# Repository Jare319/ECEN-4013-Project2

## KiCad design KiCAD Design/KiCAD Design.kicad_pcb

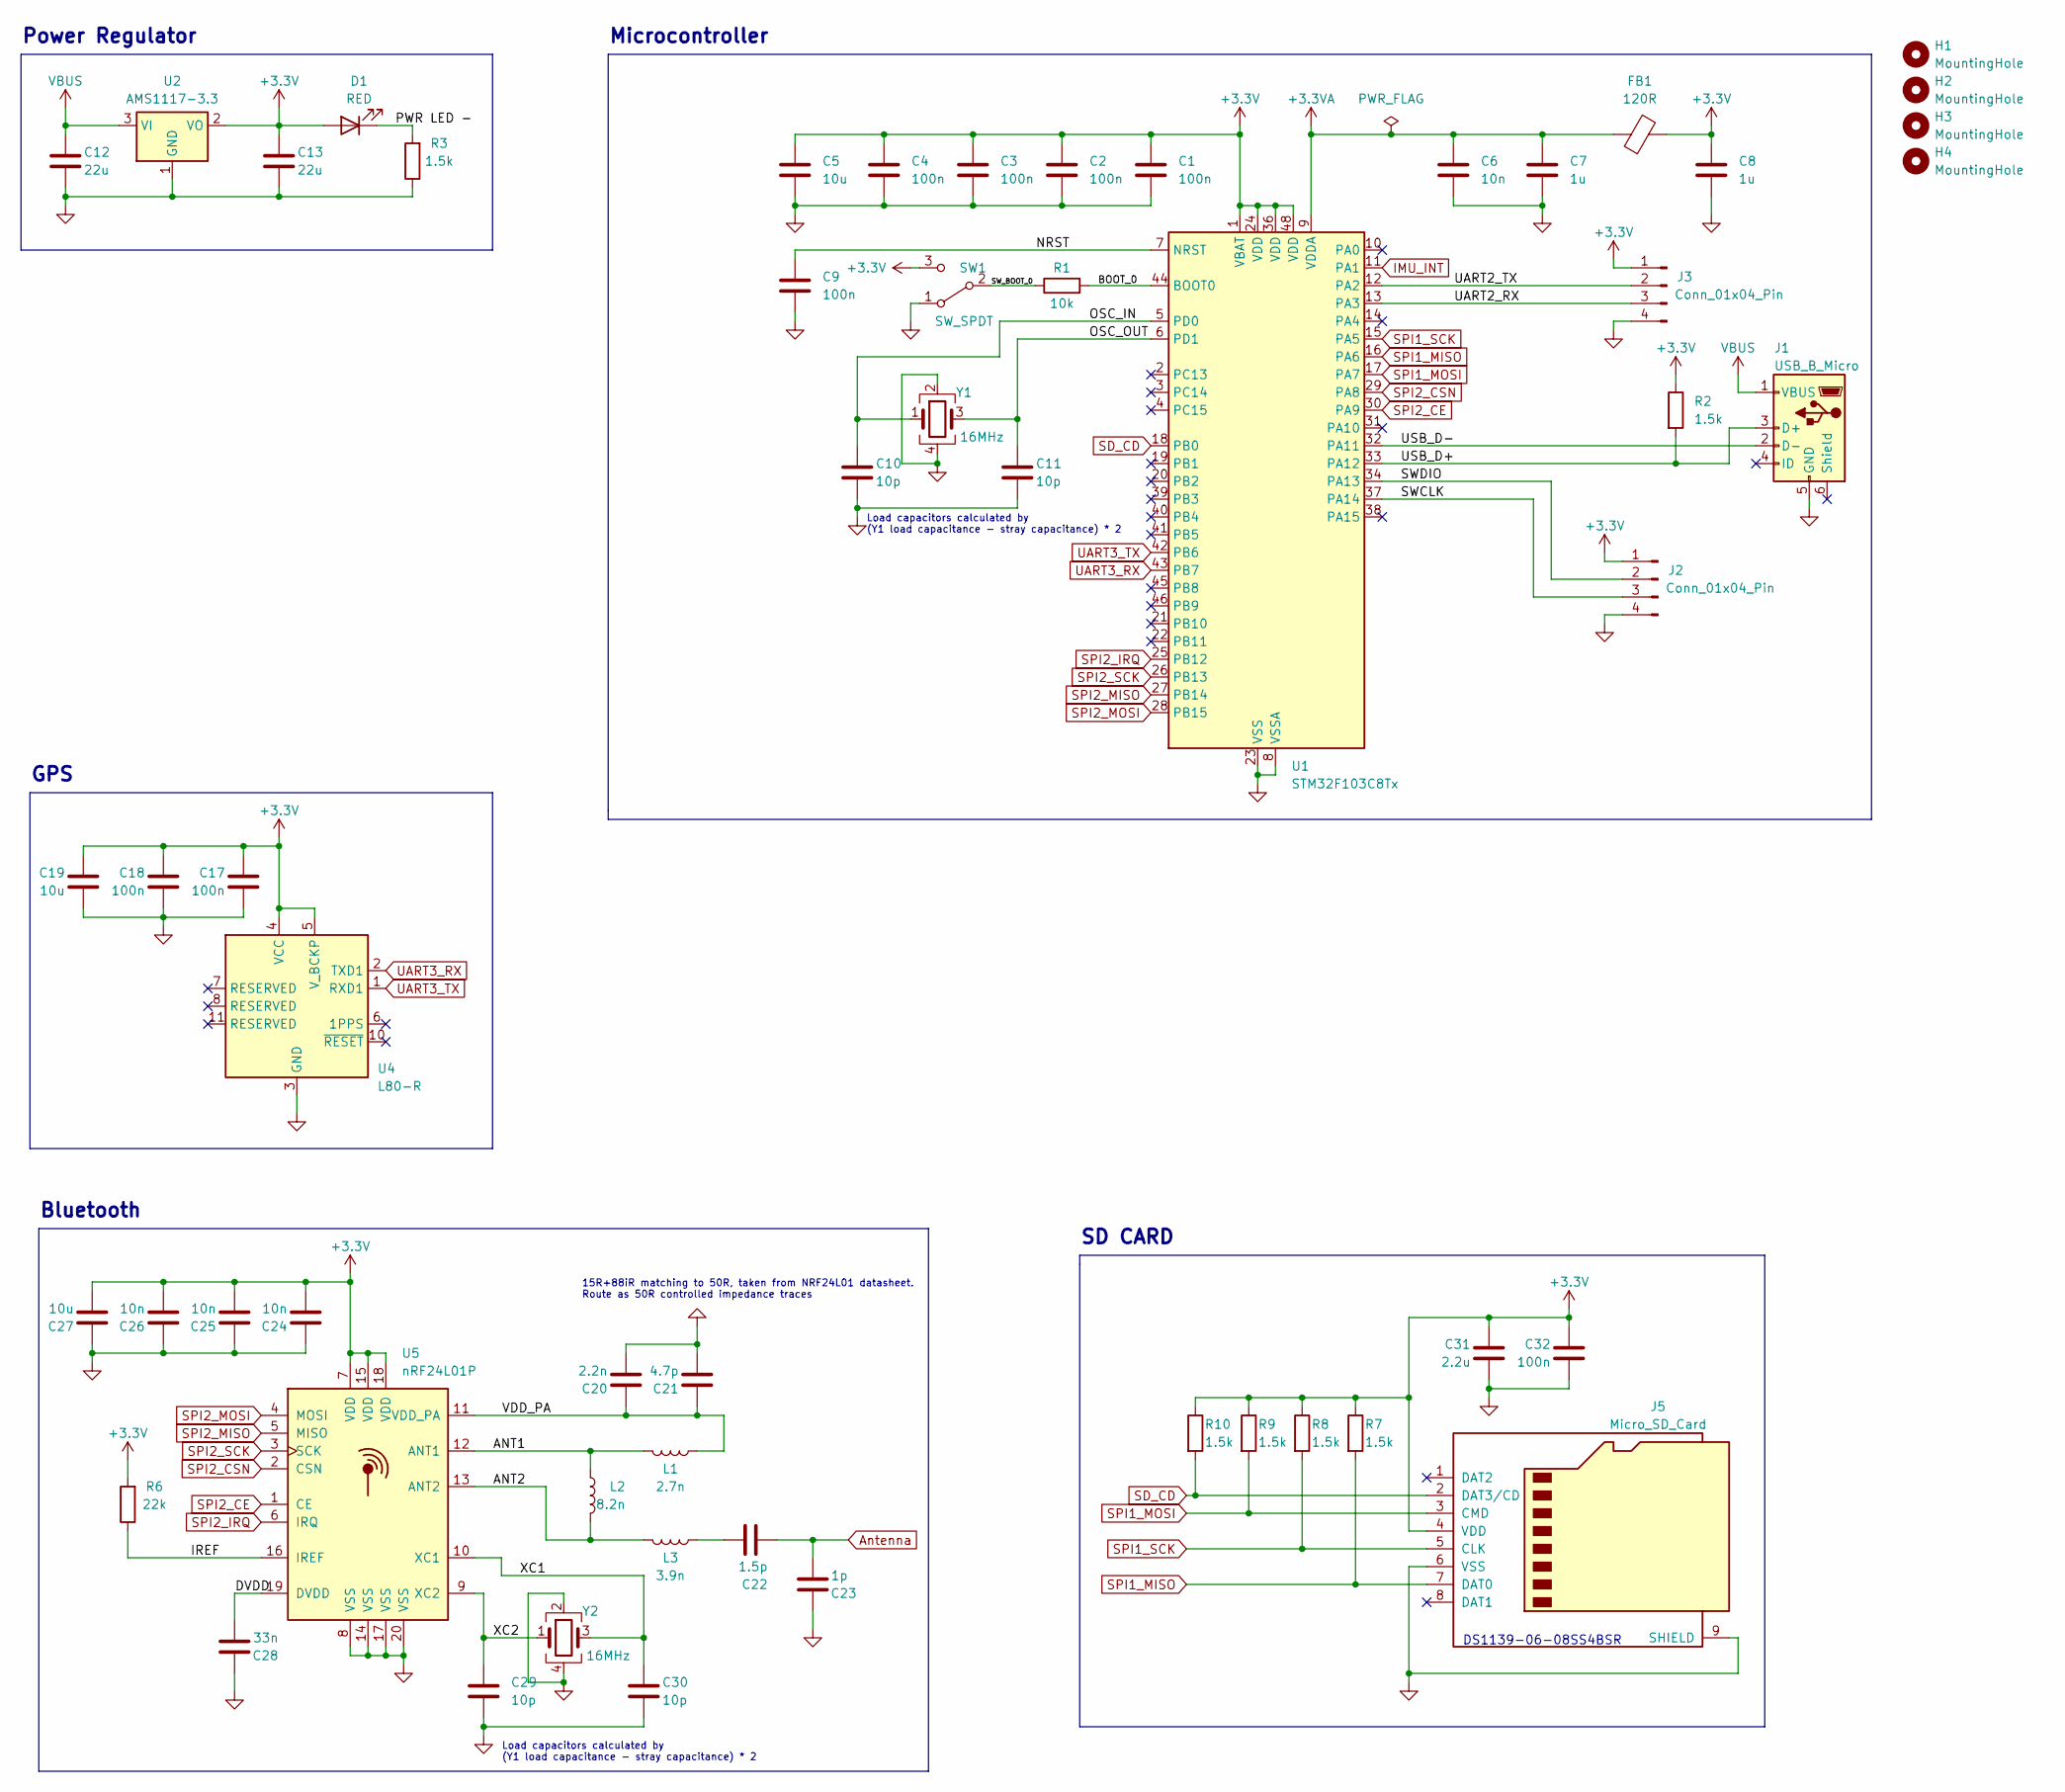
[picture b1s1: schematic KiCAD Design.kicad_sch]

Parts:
C1, C2, C3, C4, C9, C17, C18, C32: 100n; C_0402_1005Metric
C5, C19, C27: 10u; C_0603_1608Metric
C6, C24, C25, C26: 10n; C_0402_1005Metric
C7, C8: 1u; C_0402_1005Metric
C10, C11, C29, C30: 10p; C_0402_1005Metric
C12, C13: 22u; C_0805_2012Metric
C20: 2.2n; C_0402_1005Metric
C21: 4.7p; C_0402_1005Metric
C22: 1.5p; C_0402_1005Metric
C23: 1p; C_0402_1005Metric
C28: 33n; C_0402_1005Metric
C31: 2.2u; C_0402_1005Metric
D1: RED; LED_0603_1608Metric
FB1: 120R; L_0603_1608Metric
H1, H2, H3, H4: MountingHole; MountingHole_2.2mm_M2
J1: USB_B_Micro; USB_Micro-B_Wuerth_629105150521
J2, J3: Conn_01x04_Pin; PinHeader_1x04_P2.54mm_Vertical
J5: Micro_SD_Card; microSD_HC_Wuerth_693072010801
L1: 2.7n; L_0402_1005Metric
L2: 8.2n; L_0402_1005Metric
L3: 3.9n; L_0402_1005Metric
R1: 10k; R_0402_1005Metric
R2, R3, R7, R8, R9, R10: 1.5k; R_0402_1005Metric
R6: 22k; R_0402_1005Metric
SW1: SW_SPDT; SW_SPDT_PCM12
U1: STM32F103C8Tx; LQFP-48_7x7mm_P0.5mm
U2: AMS1117-3.3; SOT-223-3_TabPin2
U4: L80-R; Quectel_L80-R
U5: nRF24L01P; QFN-20-1EP_4x4mm_P0.5mm_EP2.5x2.5mm
Y1, Y2: 16MHz; Crystal_SMD_3225-4Pin_3.2x2.5mm

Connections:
+3.3V: C1.1, C2.1, C3.1, C4.1, C5.1, C8.1, C13.1, C17.2, C18.2, C19.2, C24.1, C25.1, C26.1, C27.1, C31.2, C32.2, D1.2 (A), FB1.2, J2.1, J3.1, J5.4 (VDD), R2.1, R6.2, R7.1, R8.1, R9.1, R10.1, SW1.3 (C), U1.1 (VBAT), U1.24 (VDD), U1.36 (VDD), U1.48 (VDD), U2.2 (VO), U4.4 (VCC), U4.5 (V_BCKP), U5.7 (VDD), U5.15 (VDD), U5.18 (VDD)
+3.3VA: C6.1, C7.1, FB1.1, U1.9 (VDDA)
/ANT1: L1.1, L2.2, U5.12 (ANT1)
/ANT2: L2.1, L3.1, U5.13 (ANT2)
/BOOT_0: R1.2, U1.44 (BOOT0)
/DVDD: C28.1, U5.19 (DVDD)
/IREF: R6.1, U5.16 (IREF)
/NRST: C9.1, U1.7 (NRST)
/OSC_IN: C10.1, U1.5 (PD0), Y1.1
/OSC_OUT: C11.1, U1.6 (PD1), Y1.3
/PWR LED -: D1.1 (K), R3.2
/SWCLK: J2.3, U1.37 (PA14)
/SWDIO: J2.2, U1.34 (PA13)
/SW_BOOT_0: R1.1, SW1.2 (B)
/UART2_RX: J3.3, U1.13 (PA3)
/UART2_TX: J3.2, U1.12 (PA2)
/USB_D+: J1.3 (D+), R2.2, U1.33 (PA12)
/USB_D-: J1.2 (D-), U1.32 (PA11)
/VDD_PA: C20.2, C21.2, L1.2, U5.11 (VDD_PA)
/XC1: C30.1, U5.10 (XC1), Y2.3
/XC2: C29.1, U5.9 (XC2), Y2.1
Antenna: C22.1, C23.1
GND: C1.2, C2.2, C3.2, C4.2, C5.2, C6.2, C7.2, C8.2, C9.2, C10.2, C11.2, C12.2, C13.2, C17.1, C18.1, C19.1, C20.1, C21.1, C23.2, C24.2, C25.2, C26.2, C27.2, C28.2, C29.2, C30.2, C31.1, C32.1, J1.5 (GND), J2.4, J3.4, J5.6 (VSS), J5.9 (SHIELD), R3.1, SW1.1 (A), U1.8 (VSSA), U1.23 (VSS), U1.35 (VSS), U1.47 (VSS), U2.1 (GND), U4.3 (GND), U4.12 (GND), U5.8 (VSS), U5.14 (VSS), U5.17 (VSS), U5.20 (VSS), Y1.2, Y1.4, Y2.2, Y2.4
IMU_INT: U1.11 (PA1)
unnamed: C22.2, L3.2
SD_CD: J5.2 (DAT3/CD), R10.2, U1.18 (PB0)
SPI1_MISO: J5.7 (DAT0), R7.2, U1.16 (PA6)
SPI1_MOSI: J5.3 (CMD), R9.2, U1.17 (PA7)
SPI1_SCK: J5.5 (CLK), R8.2, U1.15 (PA5)
SPI2_CE: U1.30 (PA9), U5.1 (CE)
SPI2_CSN: U1.29 (PA8), U5.2 (CSN)
SPI2_IRQ: U1.25 (PB12), U5.6 (IRQ)
SPI2_MISO: U1.27 (PB14), U5.5 (MISO)
SPI2_MOSI: U1.28 (PB15), U5.4 (MOSI)
SPI2_SCK: U1.26 (PB13), U5.3 (SCK)
UART3_RX: U1.43 (PB7), U4.2 (TXD1)
UART3_TX: U1.42 (PB6), U4.1 (RXD1)
VBUS: C12.1, J1.1 (VBUS), U2.3 (VI)

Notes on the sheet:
Bluetooth
DS1139-06-08SS4BSR
Load capacitors calculated by (Y1 load capacitance - stray capacitance) * 2
Microcontroller
Power Regulator
GPS
15R+88iR matching to 50R, taken from NRF24L01 datasheet. Route as 50R controlled impedance traces
SD CARD

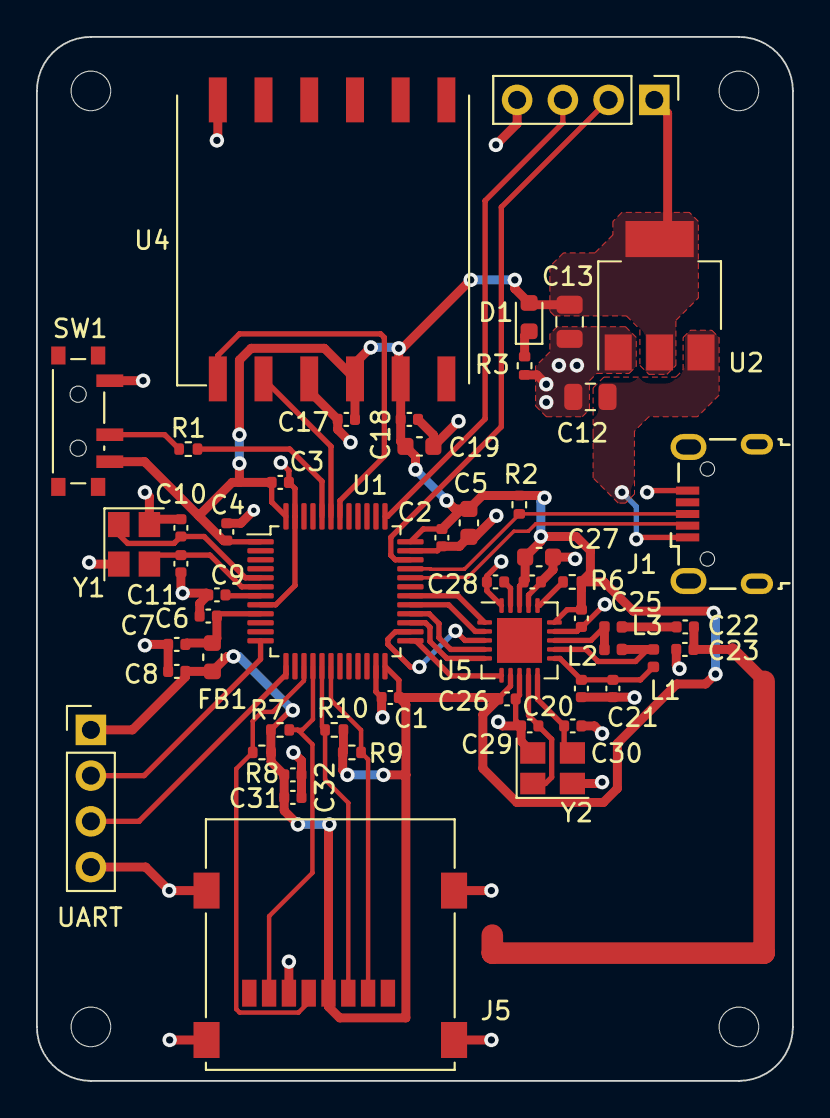
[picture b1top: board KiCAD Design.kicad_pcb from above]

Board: 2 copper layers, 42.0 x 58.0 mm, 57 parts (0 on the bottom side), 37 nets.

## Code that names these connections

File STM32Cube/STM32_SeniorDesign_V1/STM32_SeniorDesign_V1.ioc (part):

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Mcu.Name=STM32F103C(8-B)Tx
Mcu.Package=LQFP48
Mcu.UserName=STM32F103C8Tx
PA1.GPIOParameters=GPIO_Label
PA1.GPIO_Label=IMU_INT
PA1.Signal=GPIO_Input
PA11.Mode=Device
PA11.Signal=USB_DM
PA12.Mode=Device
PA12.Signal=USB_DP
PA13.Mode=Serial_Wire
PA13.Signal=SYS_JTMS-SWDIO
PA14.Mode=Serial_Wire
PA14.Signal=SYS_JTCK-SWCLK
PA2.Mode=Asynchronous
PA2.Signal=USART2_TX
PA3.Mode=Asynchronous
PA3.Signal=USART2_RX
PA5.Mode=Full_Duplex_Master
PA5.Signal=SPI1_SCK
PA6.Mode=Full_Duplex_Master
PA6.Signal=SPI1_MISO
PA7.Mode=Full_Duplex_Master
PA7.Signal=SPI1_MOSI
PA8.GPIOParameters=GPIO_Label
PA8.GPIO_Label=SPI2_IRQ
PA8.Signal=GPIO_Output
PA9.GPIOParameters=GPIO_Label
PA9.GPIO_Label=SPI2_CSN
PA9.Signal=GPIO_Output
PB0.GPIOParameters=GPIO_Label
PB0.GPIO_Label=SD_CD
PB0.Signal=GPIO_Output
PB10.Mode=Asynchronous
PB10.Signal=USART3_TX
PB11.Mode=Asynchronous
PB11.Signal=USART3_RX
PB12.GPIOParameters=GPIO_Label
PB12.GPIO_Label=SPI2_CE
PB12.Signal=GPIO_Output
PB13.Mode=Full_Duplex_Master
PB13.Signal=SPI2_SCK
PB14.Mode=Full_Duplex_Master
PB14.Signal=SPI2_MISO
PB15.Mode=Full_Duplex_Master
PB15.Signal=SPI2_MOSI
PB6.Mode=Asynchronous
PB6.Signal=USART1_TX
PB7.Mode=Asynchronous
PB7.Signal=USART1_RX
PD0-OSC_IN.Mode=HSE-External-Oscillator
PD0-OSC_IN.Signal=RCC_OSC_IN
PD1-OSC_OUT.Mode=HSE-External-Oscillator
PD1-OSC_OUT.Signal=RCC_OSC_OUT
board=custom

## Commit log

2023-10-26 Kicad schematic work
2023-10-29 Some stuff
2023-11-02 about 95% layout and routing finished
2023-11-03 All layout finished, ready to prep for order
2023-11-06 Assembly files
2023-11-06 Parts doc changes
2023-11-14 Parts updates
2023-12-02 Merging python files
2023-12-03 Initial GUI setup
2023-12-05 Refactoring + start screen
2023-12-05 Start screen almost done
2023-12-05 Uploading python files
2023-12-06 Pretty much the whole thing done
2023-12-06 Python code changes for serial writing
2023-12-06 Finished GUI
2023-12-07 Gui features finished
2023-12-16 Price breakdown
